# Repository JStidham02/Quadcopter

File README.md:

# Quadcopter

The goal of this project is to design, build, and test a quadcopter with a custom flight controller

At this point, V1 of the flight controller hardware has been designed and ordered.
V1 of the flight controller software, including a custom RTOS for the armv7e-m based microprocessor (Arm M4F on Nordic nRF52840)
is under development.

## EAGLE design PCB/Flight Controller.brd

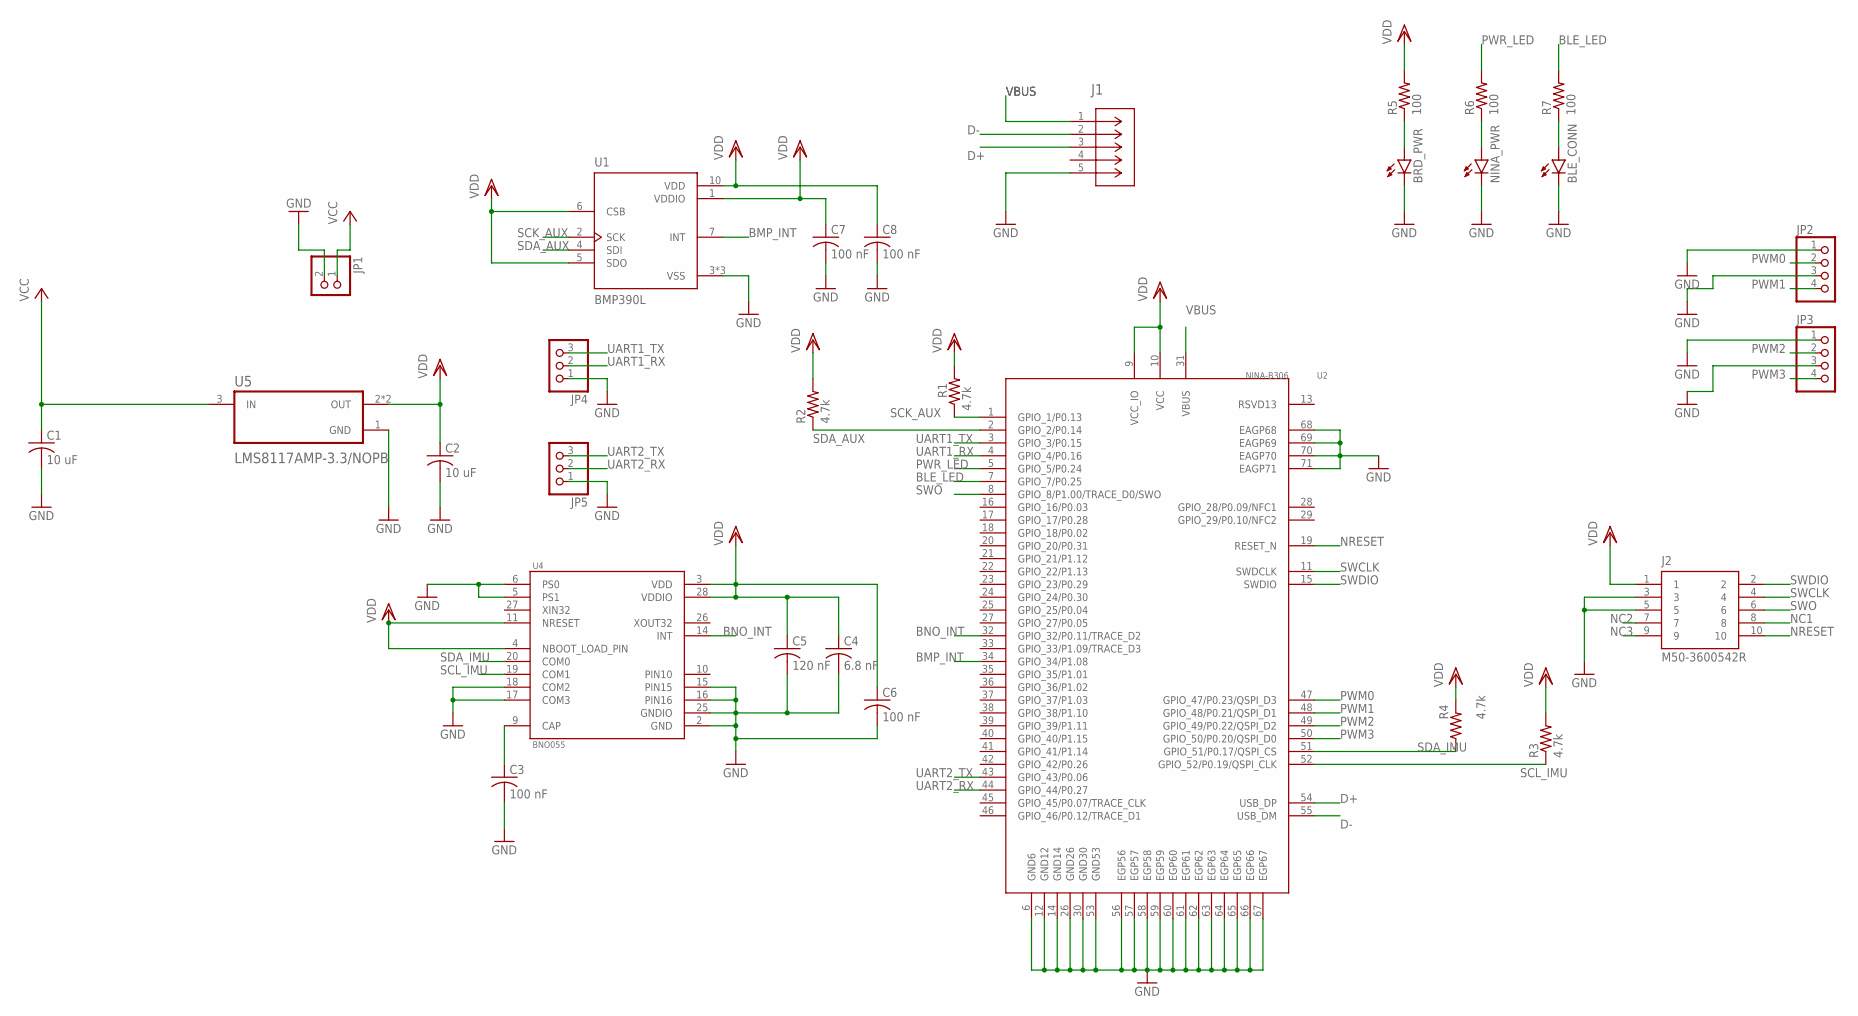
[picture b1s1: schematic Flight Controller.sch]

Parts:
BLE_CONN: LEDCHIPLED_1206; CHIPLED_1206
BRD_PWR: LEDCHIPLED_1206; CHIPLED_1206
C1, C2: 10 uF; C1206
C3, C6, C7, C8: 100 nF; C1206
C4: 6.8 nF; C1206
C5: 120 nF; C1206
J1: ZX62-AB-5PA(31); CONN5_ZX62-AB-5PA_HIR
J2: M50-3600542R; HARWIN_M50-3600542R
JP1: PINHD-1X2; 1X02
JP2, JP3: PINHD-1X4; 1X04
JP4, JP5: PINHD-1X3; 1X03
NINA_PWR: LEDCHIPLED_1206; CHIPLED_1206
R1, R2, R3, R4: 4.7k; R1206
R5, R6, R7: 100; R1206
U1: BMP390L; XDCR_BMP390L
U2: NINA-B306; NINA_LGA71R_1500X1000X223_PCB
U4: BNO055; LGA28R50P4X10_380X520X100
U5: LMS8117AMP-3.3/NOPB; SOT230P700X180-4N

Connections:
BLE_LED: R7.2, U2.7 (GPIO_7/P0.25)
BMP_INT: U1.7 (INT), U2.34 (GPIO_34/P1.08)
BNO_INT: U2.32 (GPIO_32/P0.11/TRACE_D2), U4.14 (INT)
D+: J1.3 (D+), U2.54 (USB_DP)
D-: J1.2 (D-), U2.55 (USB_DM)
GND: BLE_CONN.C, BRD_PWR.C, C1.2, C2.2, C3.2, C4.2, C5.2, C6.2, C7.2, C8.2, J1.5 (GND), J2.3, J2.5, JP1.2, JP2.1, JP2.3, JP3.1, JP3.3, JP4.1, JP5.1, NINA_PWR.C, U1.3 (VSS), U1.8 (VSS), U1.9 (VSS), U2.6 (GND6), U2.12 (GND12), U2.14 (GND14), U2.26 (GND26), U2.30 (GND30), U2.53 (GND53), U2.56 (EGP56), U2.57 (EGP57), U2.58 (EGP58), U2.59 (EGP59), U2.60 (EGP60), U2.61 (EGP61), U2.62 (EGP62), U2.63 (EGP63), U2.64 (EGP64), U2.65 (EGP65), U2.66 (EGP66), U2.67 (EGP67), U2.68 (EAGP68), U2.69 (EAGP69), U2.70 (EAGP70), U2.71 (EAGP71), U4.2 (GND), U4.5 (PS1), U4.6 (PS0), U4.15 (PIN15), U4.16 (PIN16), U4.17 (COM3), U4.18 (COM2), U4.25 (GNDIO), U5.1 (GND)
unnamed: BRD_PWR.A, R5.1
unnamed: NINA_PWR.A, R6.1
unnamed: BLE_CONN.A, R7.1
unnamed: C3.1, U4.9 (CAP)
NC1: J2.8
NC2: J2.7
NC3: J2.9
NRESET: J2.10, U2.19 (RESET_N)
PIN10: U4.10 (PIN10)
PWM0: JP2.2, U2.47 (GPIO_47/P0.23/QSPI_D3)
PWM1: JP2.4, U2.48 (GPIO_48/P0.21/QSPI_D1)
PWM2: JP3.2, U2.49 (GPIO_49/P0.22/QSPI_D2)
PWM3: JP3.4, U2.50 (GPIO_50/P0.20/QSPI_D0)
PWR_LED: R6.2, U2.5 (GPIO_5/P0.24)
SCK_AUX: R1.1, U1.2 (SCK), U2.1 (GPIO_1/P0.13)
SCL_IMU: R3.1, U2.52 (GPIO_52/P0.19/QSPI_CLK), U4.19 (COM1)
SDA_AUX: R2.1, U1.4 (SDI), U2.2 (GPIO_2/P0.14)
SDA_IMU: R4.1, U2.51 (GPIO_51/P0.17/QSPI_CS), U4.20 (COM0)
SWCLK: J2.4, U2.11 (SWDCLK)
SWDIO: J2.2, U2.15 (SWDIO)
SWO: J2.6, U2.8 (GPIO_8/P1.00/TRACE_D0/SWO)
UART1_RX: JP4.2, U2.4 (GPIO_4/P0.16)
UART1_TX: JP4.3, U2.3 (GPIO_3/P0.15)
UART2_RX: JP5.2, U2.44 (GPIO_44/P0.27)
UART2_TX: JP5.3, U2.43 (GPIO_43/P0.06)
VBUS: J1.1 (VCC), U2.31 (VBUS)
VCC: C1.1, JP1.1, U5.3 (IN)
VDD: C2.1, C4.1, C5.1, C6.1, C7.1, C8.1, J2.1, R1.2, R2.2, R3.2, R4.2, R5.2, U1.1 (VDDIO), U1.5 (SDO), U1.6 (CSB), U1.10 (VDD), U2.9 (VCC_IO), U2.10 (VCC), U4.3 (VDD), U4.4 (NBOOT_LOAD_PIN), U4.11 (NRESET), U4.28 (VDDIO), U5.2 (OUT), U5.4 (OUT)

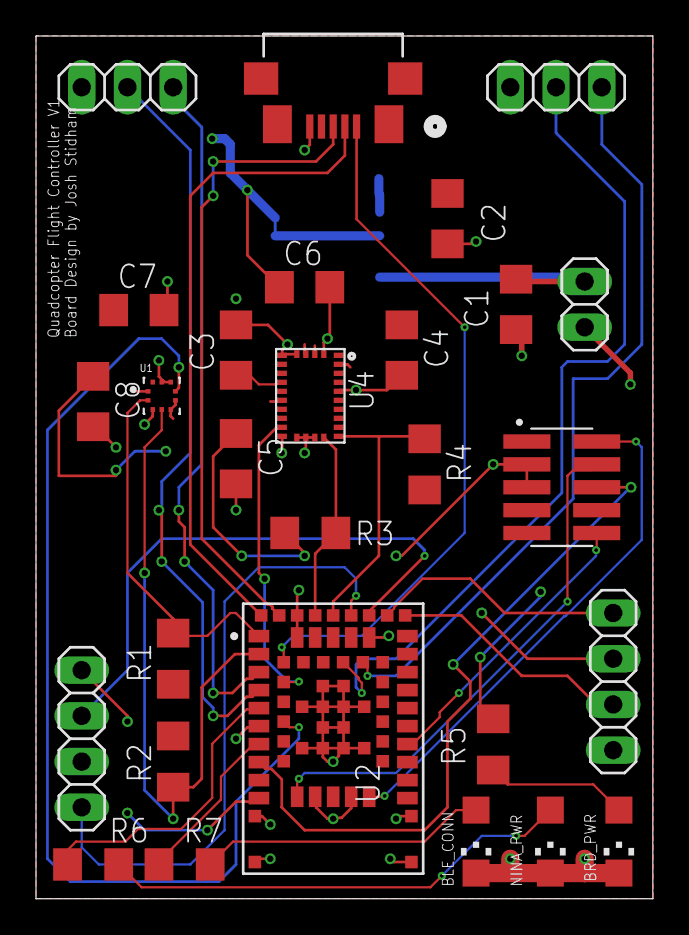
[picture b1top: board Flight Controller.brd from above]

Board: 2 copper layers, 34.3 x 47.9 mm, 29 parts (1 on the bottom side), 30 nets.

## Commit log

2022-05-09 defined basic requirements and updated readme
2022-05-09 updated goals
2022-05-10 further refiend goals
2022-05-10 updated ICs + Sensors List
2022-06-11 Updated text files to reflect currently available components
2022-06-17 Updated IC+Sensor list to reflect currently in-stock components
2022-06-17 started work on PCB design
2022-06-17 started developing design verification checklist for PCB
2022-06-17 added list of gpios that are analog and/or non radio-sensitive
2022-06-17 Started sheeto track components for PCB
2022-06-17 Added I2C Pull up resistors to PCB checklist
2022-06-17 list to track Nina peripheral usage
2022-06-17 Made I2C connections on PCB
2022-06-17 added I2C pins to notable pins list
2022-06-23 added UART and PWMs to NINA on schematic
2022-06-23 updated notable pins document to reflect UARTs and PWMs
2022-06-24 added LEDs to PCB
2022-06-24 added led pins to reflect changes to schematic
2022-06-24 Added required capacitors to begin board layout
2022-06-26 added power and PWM pinheaders to schematic
2022-06-27 began routing PCB
2022-07-22 continued work on PCB layout and added new headers for UARTs
2022-07-24 updated to contain all non-passive components from PCB
2022-07-24 PCB signals routed, only power and ground planes left
2022-07-26 replaced voltage regulator with SOT-223 package, reviewed board and is ready to order
2022-07-29 widened power traces
2022-07-29 updated silkscreen and processed CAM job
2022-07-30 added gitignore
2022-07-30 created build framework for RTOS
2022-07-30 updated gitignore
2022-07-30 updated gitignore for real this time
2022-07-30 added startup files to initialize clocks and enable ICache
2022-08-05 set up SystemInit to start FPU
2022-08-06 updated kernel directory structure and gitignore
2022-08-06 cleaned up gitignore and removed unnecessecary build files from git repo
2022-08-06 wrote heap initialization code, working on malloc, free, and verify_heap
2022-08-06 updated descriptions of each function
2022-08-06 wrote kmemplace to place blocks of memory in heap
2022-08-06 wrote kmalloc
2022-08-06 updated start and kerror to handle failure to initialize the heap
2022-08-07 finished kcoalesce and kfree heap management functions
2022-08-07 finished kverify_heap function to check heap integrity
2022-08-07 wrote assembly portion of interrupts (interfacing with Special Purpose Registers)
2022-08-07 changed many instances of term interrupt to exception to reflect architecture terminology
2022-08-16 forgot to commit for a while, finished initial development of kexceptions and began work on ktiming

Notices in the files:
parts and their libraries:
COPYRIGHT: Copyright (C) 2022 Ultra Librarian. All rights reserved.
